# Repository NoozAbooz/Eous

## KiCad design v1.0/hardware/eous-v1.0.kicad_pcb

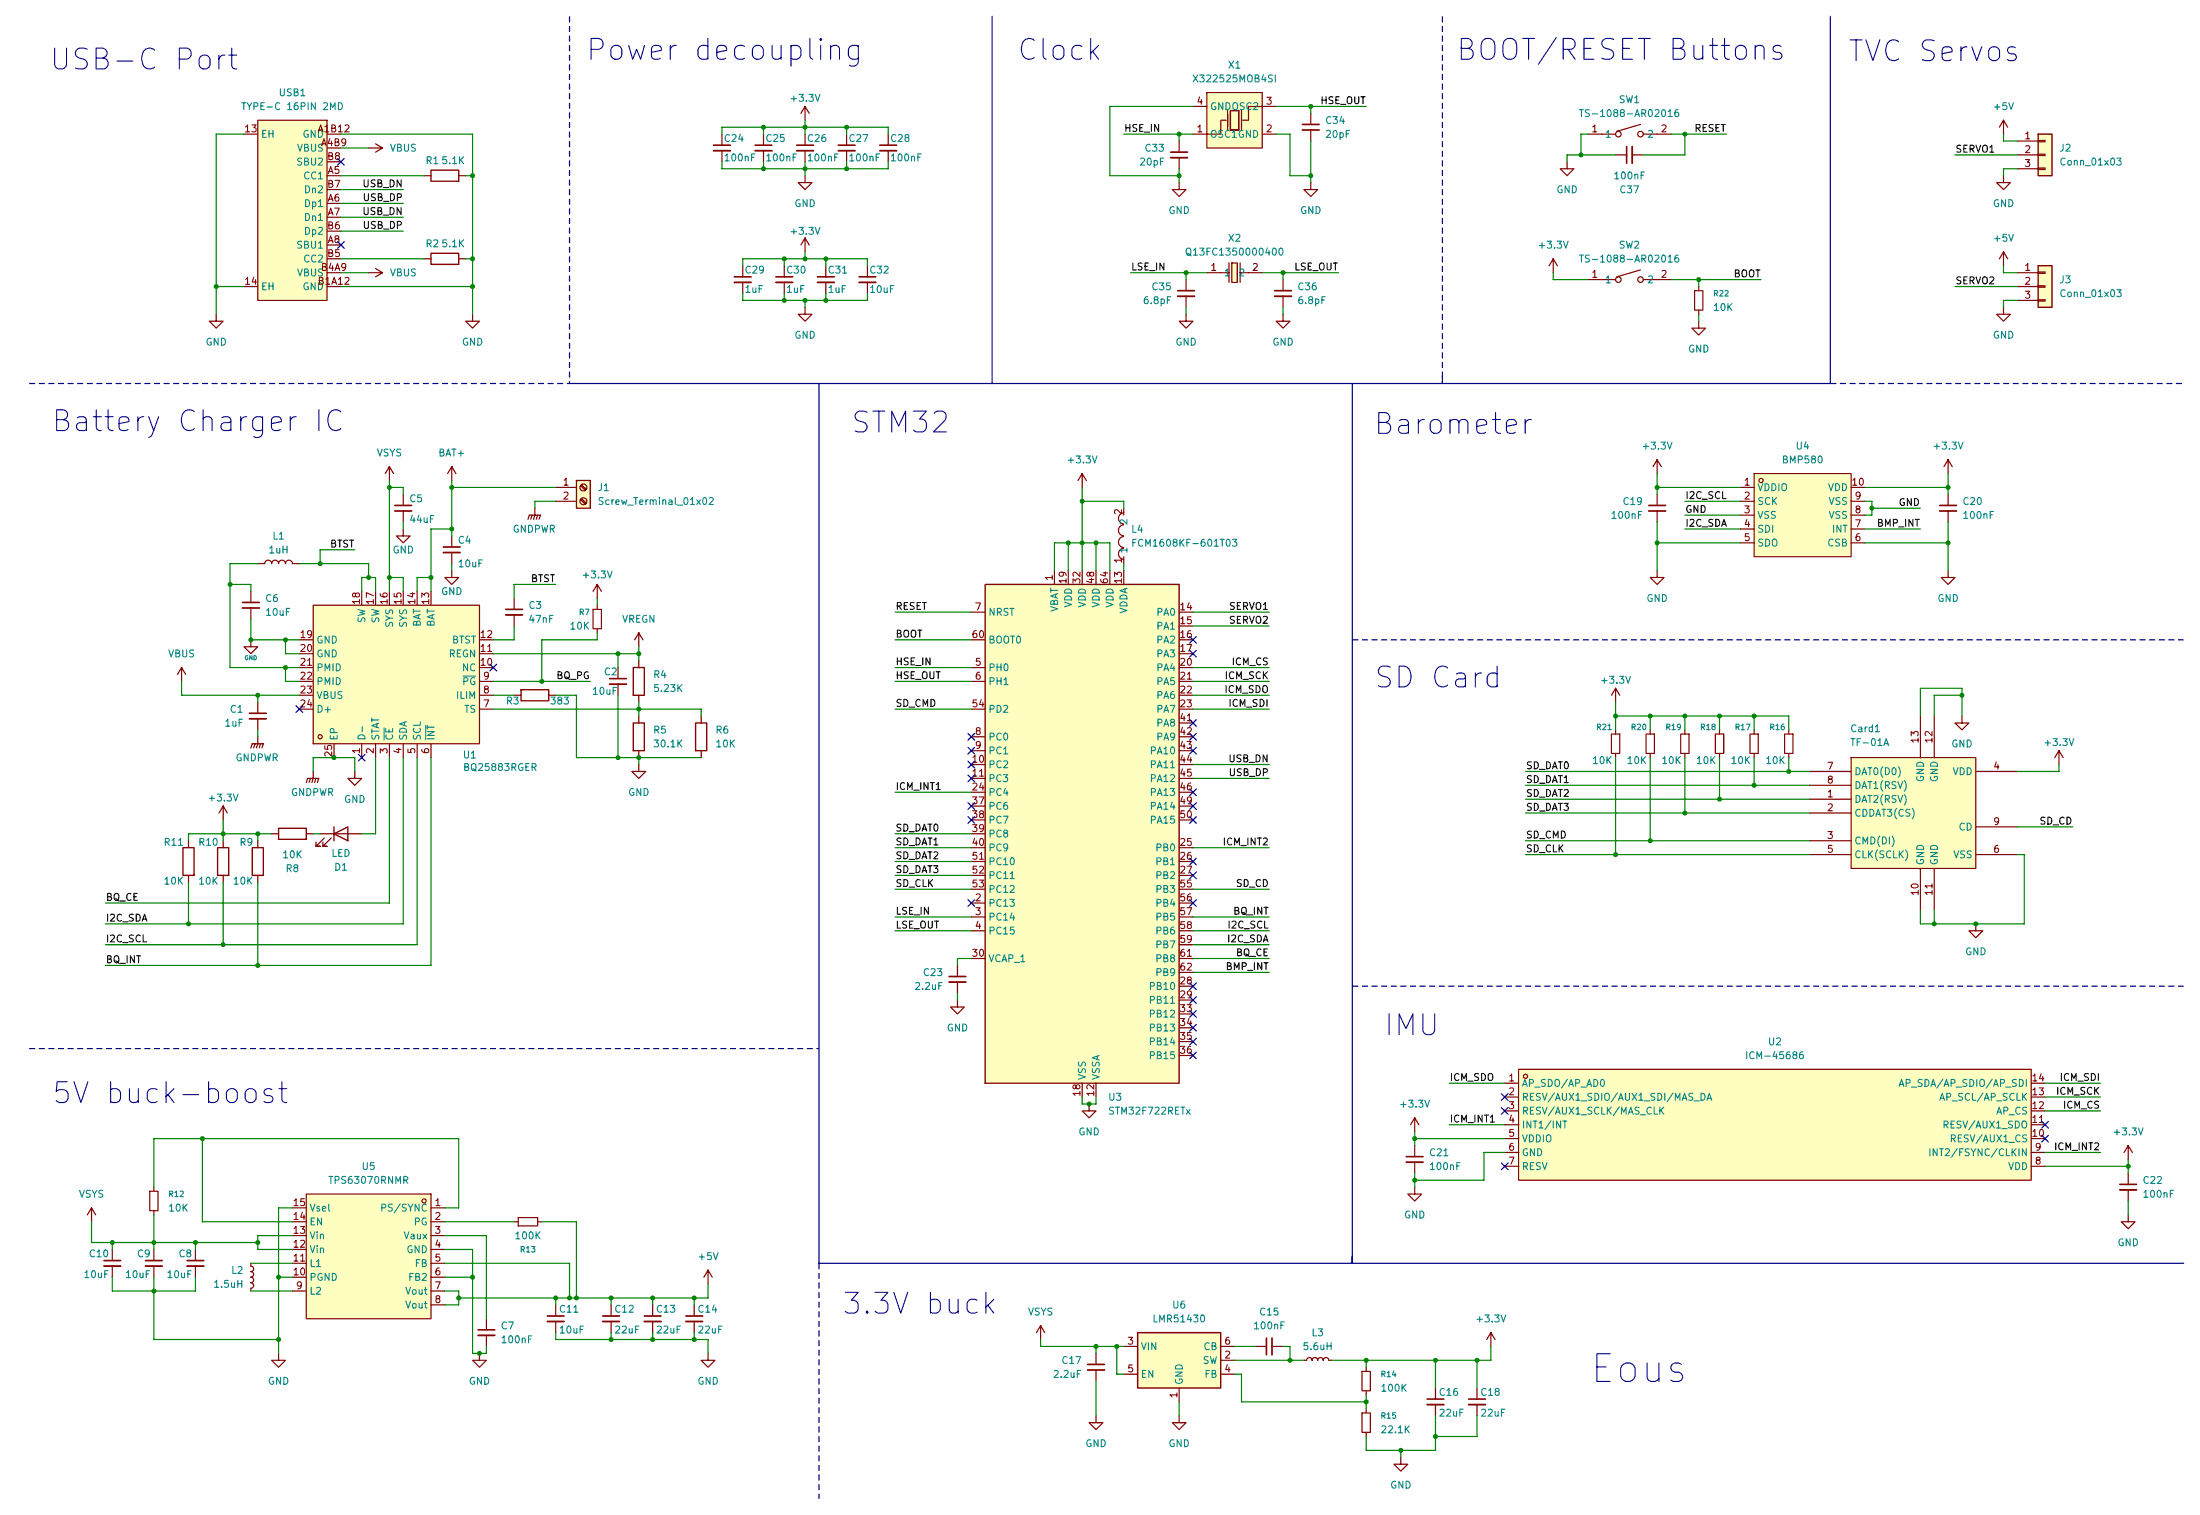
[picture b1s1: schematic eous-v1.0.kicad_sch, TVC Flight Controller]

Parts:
C1, C29, C30, C31: 1uF; C_0402_1005Metric
C2, C6, C32: 10uF; C_0402_1005Metric
C3: 47nF; C_0201_0603Metric
C4, C8, C11: 10uF; C_0603_1608Metric
C5: 44uF; C_0603_1608Metric
C7, C15, C19, C20, C21, C22, C24, C25, C26, C27, C28, C37: 100nF; C_0201_0603Metric
C9, C10: 10uF; C_0805_2012Metric
C12, C13, C14: 22uF; C_0805_2012Metric
C16, C18: 22uF; C_0402_1005Metric
C17: 2.2uF; C_0603_1608Metric
C23: 2.2uF; C_0201_0603Metric
C33, C34: 20pF; C_0201_0603Metric
C35, C36: 6.8pF; C_0201_0603Metric
Card1: TF-01A; TF-SMD_TF-01A; MPN TF-01A; LCSC Part C91145
D1: LED; LED_0402_1005Metric
J1: Screw_Terminal_01x02; TerminalBlock_Xinya_XY308-2.54-2P_1x02_P2.54mm_Horizontal
J2, J3: Conn_01x03; PinHeader_1x03_P2.54mm_Vertical
L1: 1uH; L2520
L2: 1.5uH; IND-SMD_L4.0-W4.0-A
L3: 5.6uH; IND-SMD_L3.0-W3.0
L4: FCM1608KF-601T03; L0603; MPN FCM1608KF-601T03; LCSC Part C141723
R1, R2: 5.1K; R_0201_0603Metric
R3: 383; R_0201_0603Metric
R4: 5.23K; R_0201_0603Metric
R5: 30.1K; R_0201_0603Metric
R6, R7, R8, R9, R10, R11, R12, R16, R17, R18, R19, R20, R21, R22: 10K; R_0201_0603Metric
R13, R14: 100K; R_0402_1005Metric
R15: 22.1K; R_0402_1005Metric
SW1, SW2: TS-1088-AR02016; SW-SMD_L3.9-W3.0-P4.45; MPN TS-1088-AR02016; LCSC Part C720477
U1: BQ25883RGER; VFQFPN-24_L4.0-W4.0-P0.50-BL-EP2.8; MPN BQ25883RGER; LCSC Part C544362
U2: ICM-45686; LGA-14_L3.0-W2.5-P0.50-TL; MPN ICM-45686; LCSC Part C22459454
U3: STM32F722RETx; LQFP-64_10x10mm_P0.5mm
U4: BMP580; LGA-10_L2.0-W2.0-P0.50-TL_BMP580; MPN BMP580; LCSC Part C22391138
U5: TPS63070RNMR; VQFN-15_L3.0-W2.5-P0.50-BL; MPN TPS63070RNMR; LCSC Part C109322
U6: LMR51430; SOT-23-6
USB1: TYPE-C 16PIN 2MD; USB-C-SMD_TYPE-C-16PIN-2MD-073; MPN TYPE-C 16PIN 2MD(073); LCSC Part C2765186
X1: X322525MOB4SI; CRYSTAL-SMD_4P-L3.2-W2.5-BL; MPN X322525MOB4SI; LCSC Part C9006
X2: Q13FC1350000400; FC-135R_L3.2-W1.5; MPN Q13FC13500004; LCSC Part C32346

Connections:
+3.3V: C16.1, C18.1, C19.1, C20.1, C21.1, C22.1, C24.1, C25.1, C26.1, C27.1, C28.1, C29.1, C30.1, C31.1, C32.1, Card1.4 (VDD), L3.2, L4.2, R7.1, R8.1, R9.1, R10.1, R11.1, R14.1, R16.1, R17.1, R18.1, R19.1, R20.1, R21.1, SW2.1, U2.5 (VDDIO), U2.8 (VDD), U3.1 (VBAT), U3.19 (VDD), U3.32 (VDD), U3.48 (VDD), U3.64 (VDD), U4.1 (VDDIO), U4.10 (VDD)
+5V: C11.1, C12.1, C13.1, C14.1, J2.1, J3.1, R13.2, U5.5 (FB), U5.7 (Vout), U5.8 (Vout)
/BMP_INT: U3.62 (PB9), U4.7 (INT)
/BOOT: R22.1, SW2.2, U3.60 (BOOT0)
/BQ_CE: U1.3 (~CE), U3.61 (PB8)
/BQ_INT: R9.2, U1.6 (~INT), U3.57 (PB5)
/BQ_PG: R7.2, U1.9 (~PG)
/BTST: C3.1, L1.2, U1.17 (SW), U1.18 (SW)
/HSE_IN: C33.1, U3.5 (PH0), X1.1 (OSC1)
/HSE_OUT: C34.1, U3.6 (PH1), X1.3 (OSC2)
/I2C_SCL: R10.2, U1.5 (SCL), U3.58 (PB6), U4.2 (SCK)
/I2C_SDA: R11.2, U1.4 (SDA), U3.59 (PB7), U4.4 (SDI)
/ICM_CS: U2.12 (AP_CS), U3.20 (PA4)
/ICM_INT1: U2.4 (INT1/INT), U3.24 (PC4)
/ICM_INT2: U2.9 (INT2/FSYNC/CLKIN), U3.25 (PB0)
/ICM_SCK: U2.13 (AP_SCL/AP_SCLK), U3.21 (PA5)
/ICM_SDI: U2.14 (AP_SDA/AP_SDIO/AP_SDI), U3.23 (PA7)
/ICM_SDO: U2.1 (AP_SDO/AP_AD0), U3.22 (PA6)
/LSE_IN: C35.1, U3.3 (PC14), X2.1
/LSE_OUT: C36.1, U3.4 (PC15), X2.2
/RESET: C37.2, SW1.2, U3.7 (NRST)
/SD_CD: Card1.9 (CD), U3.55 (PB3)
/SD_CLK: Card1.5 (CLK(SCLK)), R21.2, U3.53 (PC12)
/SD_CMD: Card1.3 (CMD(DI)), R20.2, U3.54 (PD2)
/SD_DAT0: Card1.7 (DAT0(D0)), R16.2, U3.39 (PC8)
/SD_DAT1: Card1.8 (DAT1(RSV)), R17.2, U3.40 (PC9)
/SD_DAT2: Card1.1 (DAT2(RSV)), R18.2, U3.51 (PC10)
/SD_DAT3: Card1.2 (CDDAT3(CS)), R19.2, U3.52 (PC11)
/SERVO1: J2.2, U3.14 (PA0)
/SERVO2: J3.2, U3.15 (PA1)
/USB_DN: U3.44 (PA11), USB1.A7 (Dn1), USB1.B7 (Dn2)
/USB_DP: U3.45 (PA12), USB1.A6 (Dp1), USB1.B6 (Dp2)
BAT+: C4.1, J1.1, U1.13 (BAT), U1.14 (BAT)
GND: C1.2, C2.2, C4.2, C5.2, C6.2, C7.2, C8.2, C9.2, C10.2, C11.2, C12.2, C13.2, C14.2, C16.2, C17.2, C18.2, C19.2, C20.2, C21.2, C22.2, C23.2, C24.2, C25.2, C26.2, C27.2, C28.2, C29.2, C30.2, C31.2, C32.2, C33.2, C34.2, C35.2, C36.2, C37.1, Card1.6 (VSS), Card1.10 (GND), Card1.11 (GND), Card1.12 (GND), Card1.13 (GND), J1.2, J2.3, J3.3, R1.2, R2.2, R3.1, R5.2, R6.2, R15.2, R22.2, SW1.1, U1.19 (GND), U1.20 (GND), U1.25 (EP), U2.6 (GND), U3.12 (VSSA), U3.18 (VSS), U3.31 (VSS), U3.47 (VSS), U3.63 (VSS), U4.3 (VSS), U4.5 (SDO), U4.6 (CSB), U4.8 (VSS), U4.9 (VSS), U5.4 (GND), U5.6 (FB2), U5.10 (PGND), U5.15 (Vsel), U6.1 (GND), USB1.13 (EH), USB1.14 (EH), USB1.A1B12 (GND), USB1.B1A12 (GND), X1.2 (GND), X1.4 (GND)
unnamed: C6.1, L1.1, U1.21 (PMID), U1.22 (PMID)
unnamed: D1.2 (A), U1.2 (STAT)
unnamed: D1.1 (K), R8.2
unnamed: C3.2, U1.12 (BTST)
unnamed: R3.2, U1.8 (ILIM)
unnamed: R4.2, R5.1, R6.1, U1.7 (TS)
unnamed: C23.1, U3.30 (VCAP_1)
unnamed: L4.1, U3.13 (VDDA)
unnamed: R12.1, U5.1 (PS/SYNC), U5.14 (EN)
unnamed: L2.1, U5.11 (L1)
unnamed: L2.2, U5.9 (L2)
unnamed: R13.1, U5.2 (PG)
unnamed: C7.1, U5.3 (Vaux)
unnamed: C15.1, U6.6 (CB)
unnamed: R14.2, R15.1, U6.4 (FB)
unnamed: C15.2, L3.1, U6.2 (SW)
unnamed: R1.1, USB1.A5 (CC1)
unnamed: R2.1, USB1.B5 (CC2)
VBUS: C1.1, U1.23 (VBUS), USB1.A4B9 (VBUS), USB1.B4A9 (VBUS)
VREGN: C2.1, R4.1, U1.11 (REGN)
VSYS: C5.1, C8.1, C9.1, C10.1, C17.1, R12.2, U1.15 (SYS), U1.16 (SYS), U5.12 (Vin), U5.13 (Vin), U6.3 (VIN), U6.5 (EN)

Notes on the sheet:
STM32
SD Card
Battery Charger IC
Power decoupling
Clock
5V buck-boost
Barometer
3.3V buck
TVC Servos
BOOT/RESET Buttons
Eous
IMU
USB-C Port

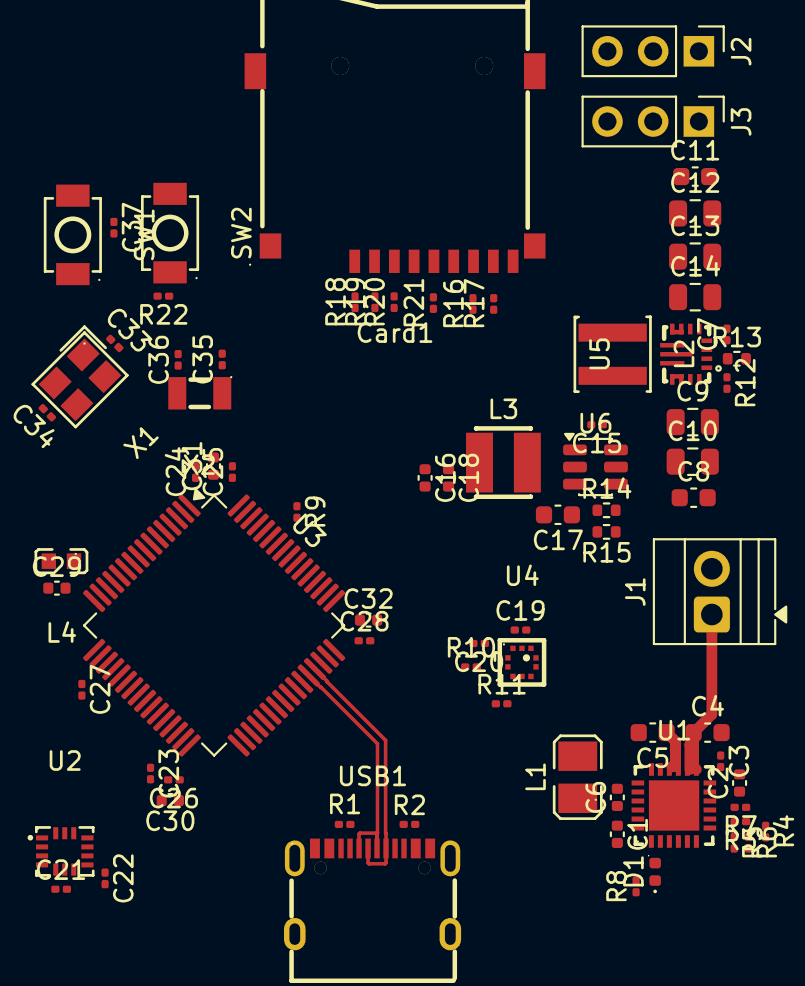
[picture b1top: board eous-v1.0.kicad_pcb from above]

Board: 2 copper layers, 79 parts (0 on the bottom side), 55 nets.

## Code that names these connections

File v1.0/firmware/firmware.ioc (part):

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Mcu.Name=STM32F722R(C-E)Tx
Mcu.Package=LQFP64
Mcu.UserName=STM32F722RETx
PA0-WKUP.Signal=S_TIM2_CH1_ETR
PA1.Signal=S_TIM2_CH2
PA11.Mode=Host_Only
PA11.Signal=USB_OTG_FS_DM
PA12.Mode=Host_Only
PA12.Signal=USB_OTG_FS_DP
PA4.Mode=NSS_Signal_Hard_Output
PA4.Signal=SPI1_NSS
PA5.Mode=Full_Duplex_Master
PA5.Signal=SPI1_SCK
PA6.Mode=Full_Duplex_Master
PA6.Signal=SPI1_MISO
PA7.Mode=Full_Duplex_Master
PA7.Signal=SPI1_MOSI
PB0.GPIOParameters=GPIO_Label
PB0.GPIO_Label=ICM_INT2
PB0.Signal=GPXTI0
PB3.GPIOParameters=GPIO_Label
PB3.GPIO_Label=SD_CD
PB3.Signal=GPIO_Input
PB5.GPIOParameters=GPIO_Label
PB5.GPIO_Label=BQ_INT
PB5.Signal=GPXTI5
PB6.Mode=I2C
PB6.Signal=I2C1_SCL
PB7.Mode=I2C
PB7.Signal=I2C1_SDA
PB8.GPIOParameters=GPIO_Label
PB8.GPIO_Label=BQ_CE
PB8.Signal=GPIO_Output
PB9.GPIOParameters=GPIO_Label
PB9.GPIO_Label=BMP_INT
PB9.Signal=GPXTI9
PC10.Mode=SD_4_bits_Wide_bus
PC10.Signal=SDMMC1_D2
PC11.Mode=SD_4_bits_Wide_bus
PC11.Signal=SDMMC1_D3
PC12.Mode=SD_4_bits_Wide_bus
PC12.Signal=SDMMC1_CK
PC14-OSC32_IN.Mode=LSE-External-Oscillator
PC14-OSC32_IN.Signal=RCC_OSC32_IN
PC15-OSC32_OUT.Mode=LSE-External-Oscillator
PC15-OSC32_OUT.Signal=RCC_OSC32_OUT
PC4.GPIOParameters=GPIO_Label
PC4.GPIO_Label=ICM_INT1
PC4.Signal=GPXTI4
PC8.Mode=SD_4_bits_Wide_bus
PC8.Signal=SDMMC1_D0
PC9.Mode=SD_4_bits_Wide_bus
PC9.Signal=SDMMC1_D1
PD2.Mode=SD_4_bits_Wide_bus
PD2.Signal=SDMMC1_CMD
PH0-OSC_IN.Mode=HSE-External-Oscillator
PH0-OSC_IN.Signal=RCC_OSC_IN
PH1-OSC_OUT.Mode=HSE-External-Oscillator
PH1-OSC_OUT.Signal=RCC_OSC_OUT
RCC.HSE_VALUE=25000000
board=custom

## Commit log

2026-05-10 Finished decoupling
2026-05-11 layout pcb
2026-05-12 pcb edits before routing
2026-05-31 update board setup
